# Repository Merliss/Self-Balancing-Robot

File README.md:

# Self-Balancing-Robot
Self balancing robot on esp32 platform.

For the project a balancing mobile robot was constructed and programmed. Balancing is
carried out parallel to the trajectory. As part of the research, simulations were carried out
in Matlab and Simulink software. In addition, theoretical issues related to the inverted
pendulum balancing problem were presented. A PID controller was implemented in the
microcontroller. The control algorithm is based on data taken from the gyroscope and
accelerometer. In addition, the control of the robot via a smartphone application using
Bluetooth communication was realized.

For the project there was created a pcb schema but not produced becasue lack of time. PCB was made in KiCad.

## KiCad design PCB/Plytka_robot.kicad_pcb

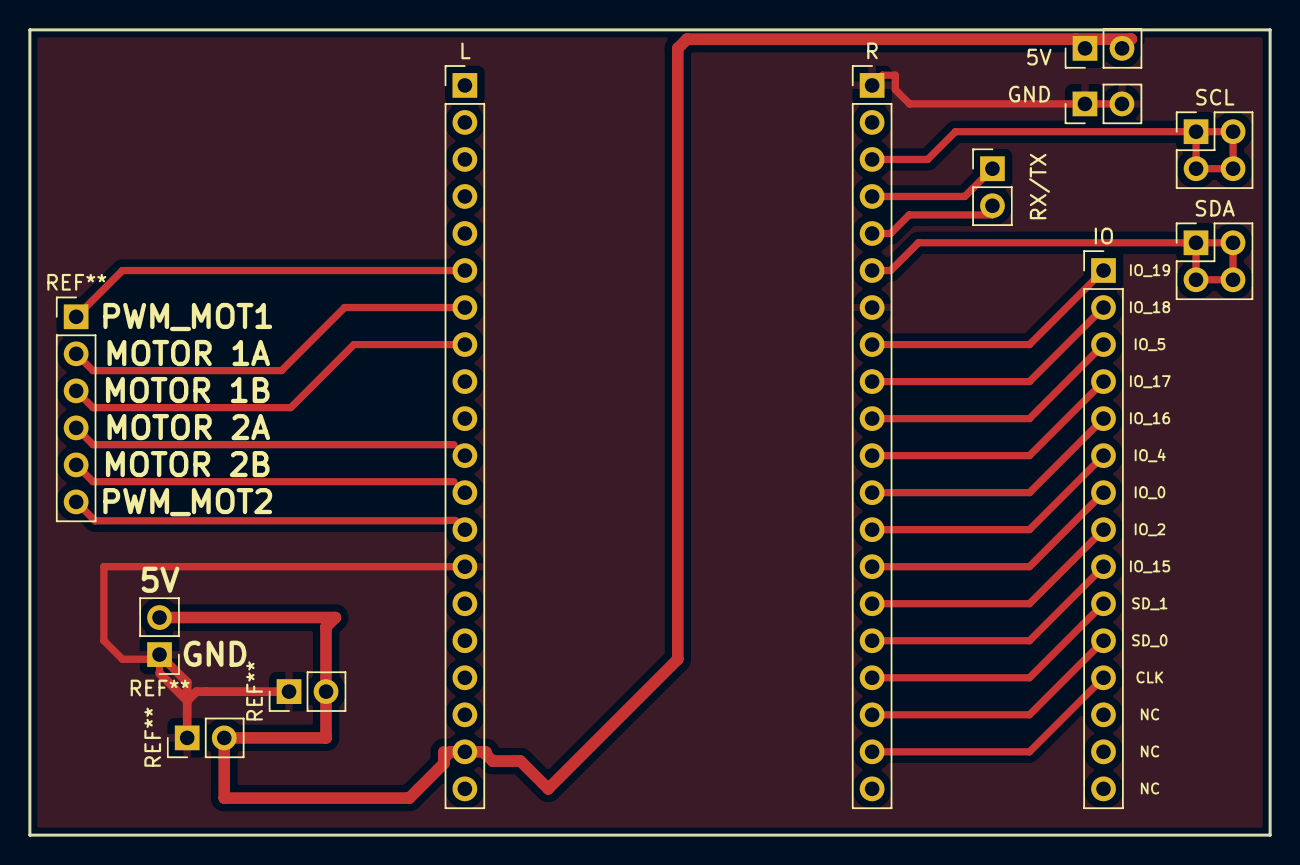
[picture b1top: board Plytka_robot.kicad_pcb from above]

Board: 2 copper layers, 85.1 x 55.2 mm, 8 parts (0 on the bottom side), 2 nets.

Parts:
5V: PinHeader_1x02_P2.54mm_Vertical
GND: PinHeader_1x02_P2.54mm_Vertical
IO: PinHeader_1x15_P2.54mm_Vertical
L: PinHeader_1x20_P2.54mm_Vertical
R: PinHeader_1x20_P2.54mm_Vertical
RX/TX: PinHeader_1x02_P2.54mm_Vertical
SCL: PinHeader_2x02_P2.54mm_Vertical
SDA: PinHeader_2x02_P2.54mm_Vertical

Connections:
+5V: 5V.1, 5V.2, L.19
GND: GND.1, GND.2, L.14, R.1, R.7

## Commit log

2023-10-02 Photos added to README
2023-10-02 File upload
2023-10-02 Libs updated
